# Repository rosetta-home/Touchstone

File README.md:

# Open Source Indoor Air Quality Sensor
An open hardware and software indoor air quality sensor provided by the [National Association of REALTORS](http://realtor.org) and [CRT Labs](https://crtlabs.org) in collaboration with the [Built Environment Research Group](http://built-envi.com/) at Illinois Institute of Technology.

**Features**:
* Can measure upto 8 indoor environmental quality parameters (listed below)
* Atmel ATmega328P 16MHz 8-bit processor (based on Arduino platform)
* Genuine FTDI chip for serial communication with host computer
* Mini RGB LED for status and notification
* Programmable button for custom actions such as reset, configuration, etc.
* Long range wireless data transfer using FSK radio (no dependence on WiFi, cellular, etc.)
* Small footprint PCB board (less than 2x2 inches or 50x50mm)
* Low power requirements (35mA idle with all sensors running, 190mA peak during wireless data transfer)

**Measurement Points**:
* Temperature (Si7021)
* Relative Humidity (Si7021)
* VOC (Volatile Organic Compounds) (CCS811/IAQ-Core)
* CO2 (MH-z19)
* Particulate Matter, PM2.5 (PMS7003)
* Barometric Pressure (BMP280)
* Light Intensity (TSL2591)
* Sound Intensity (Electret Microphone)

**Connectivity**:
* FSK radio (RFM69HW 915MHz)
* MicroUSB (FTDI FX231XQ)

License:
Apache License Version 2.0

For the Raspberry Pi HAT, please visit the [PiAQ Website](http://piaq.io) and [repository](https://github.com/NationalAssociationOfRealtors/PiAQ)

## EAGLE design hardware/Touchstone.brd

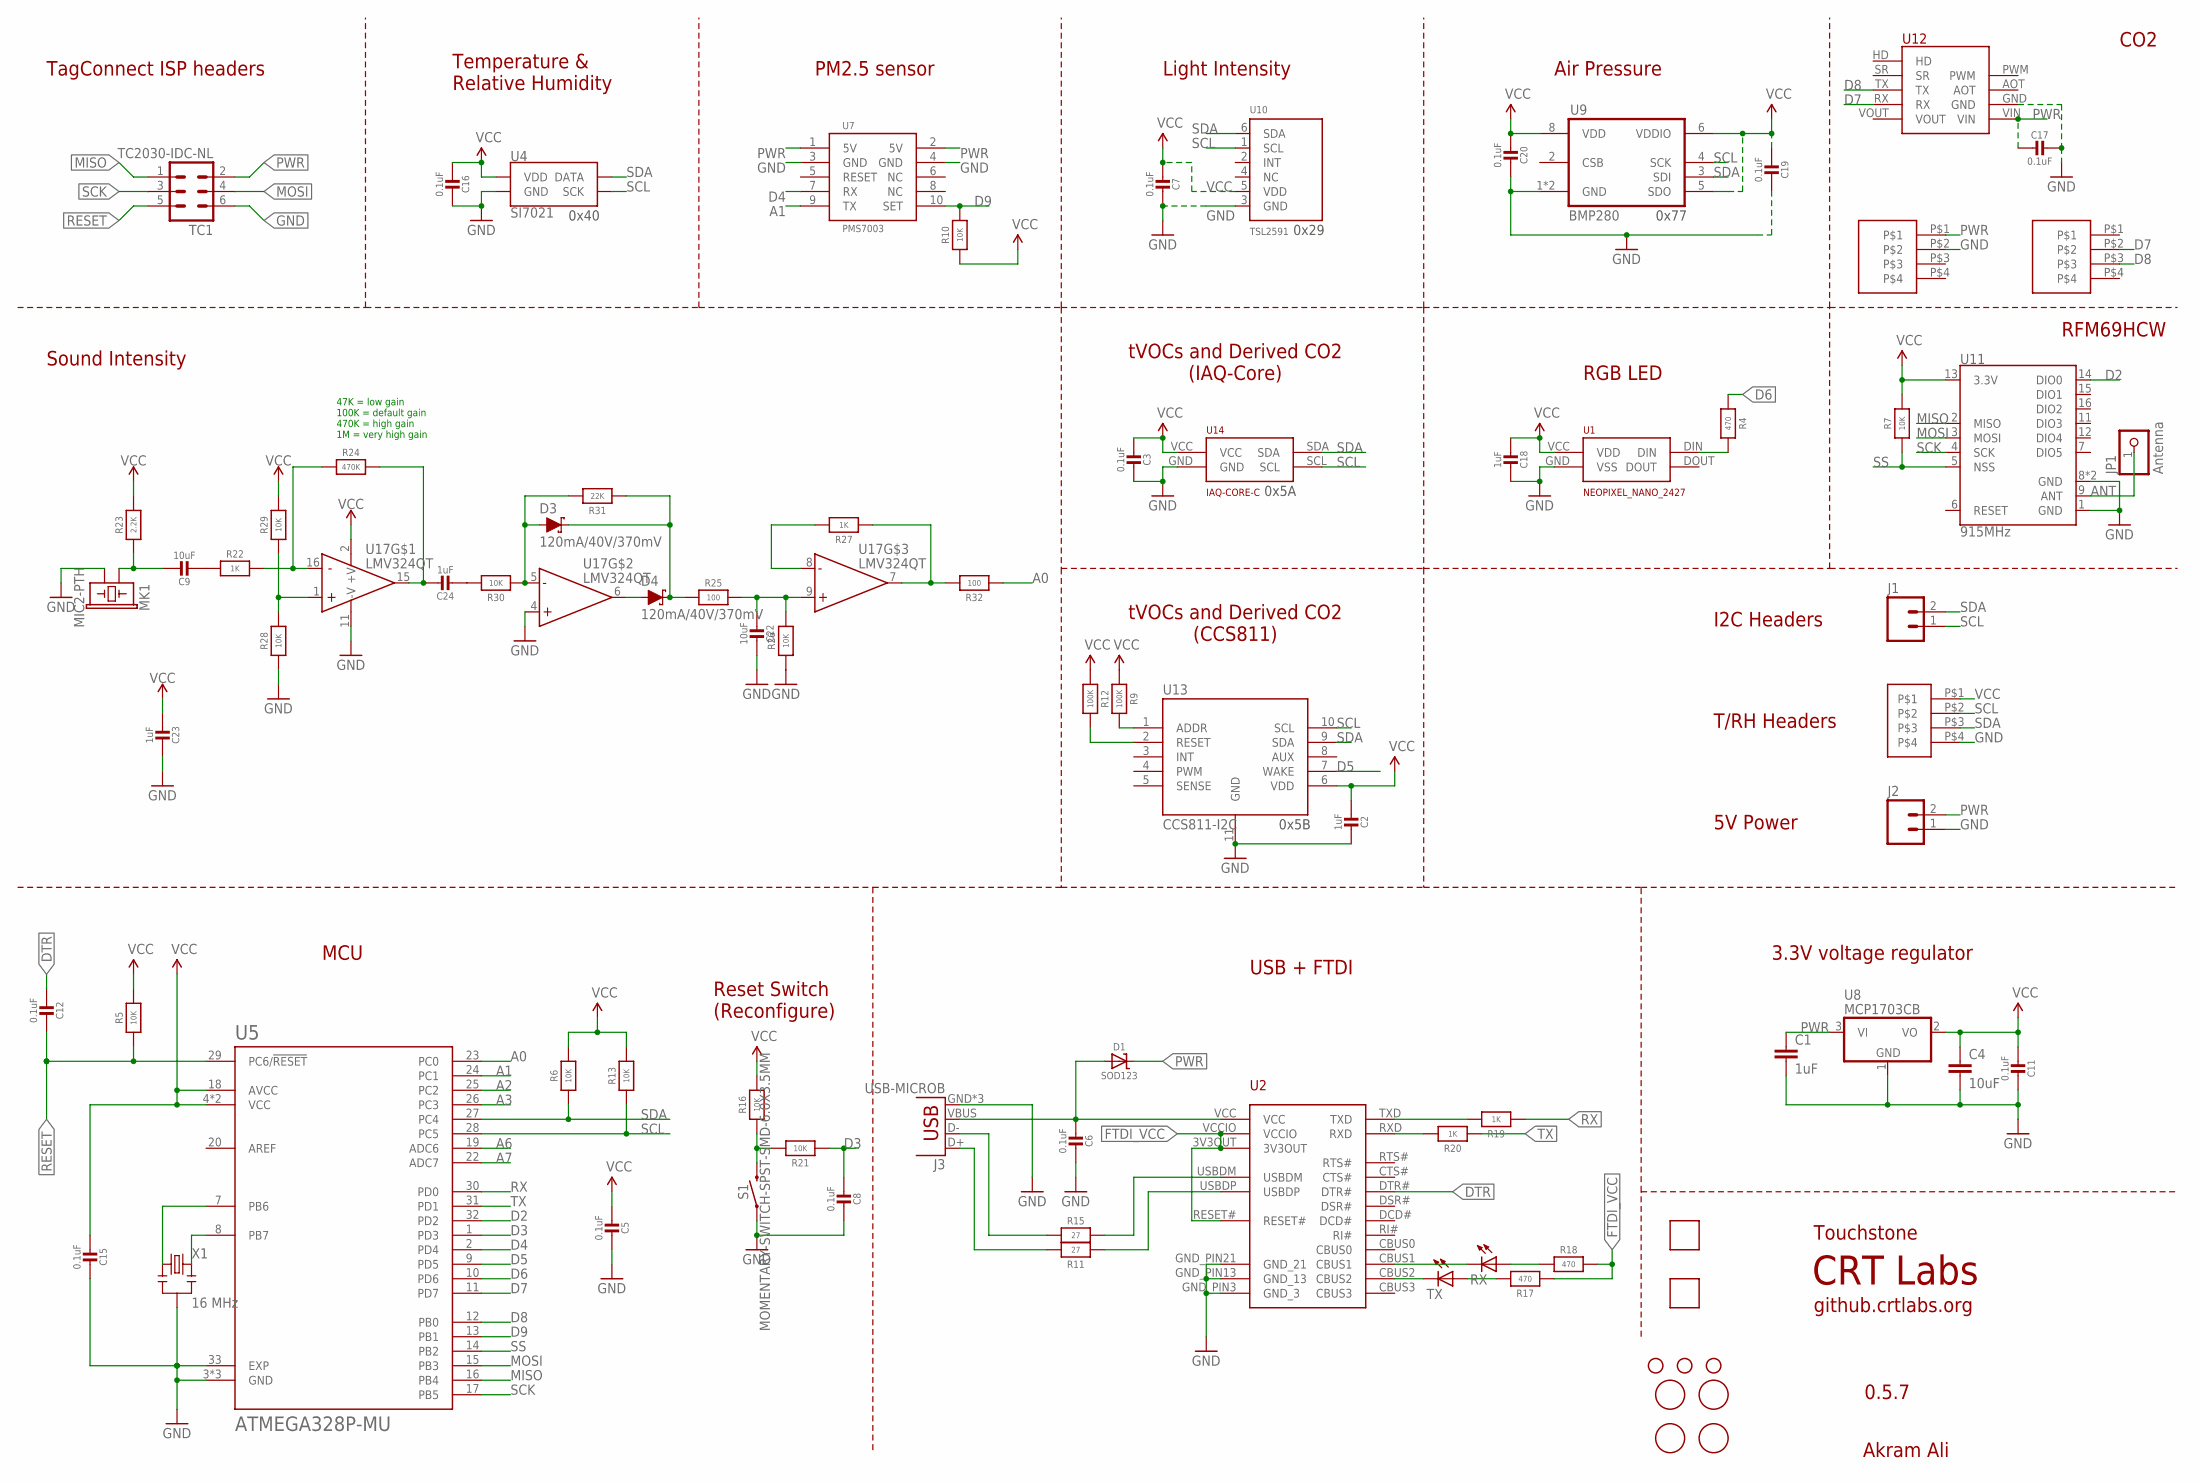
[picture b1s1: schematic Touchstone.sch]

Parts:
C1: 1uF; 0805; MPN CC0805ZRY5V8BB105
C2, C18, C23, C24: 1uF; MICROBUILDER__0402MP; MPN CC0402KRX5R6BB105
C3, C5, C6, C7, C8, C11, C12, C15, C16, C17, C19, C20: 0.1uF; MICROBUILDER__0402MP; MPN GRM155R71C104KA88J
C4: 10uF; 0805; MPN CC0805KKX5R6BB106
C9, C22: 10uF; MICROBUILDER__0402MP; MPN GRJ155R60J106ME11D
D1: SOD123; MICROBUILDER_SOD-123; MPN SD103AW-13-F
D3, D4: 120mA/40V/370mV; SOD-523; MPN RB751S40T1G
H1, H2, H3: STAND-OFF
J1, J2: M02PTH; 1X02
J3: USB-MICROB; MPN ZX62-B-5PA(33)
JP1: Antenna; 1X01-CLEANBIG; MPN Helical antenna
MK1: MIC2-PTH; MICROPHONE-PTH-4.0MM; MPN TOM-1545P-R
R4, R17, R18: 470; MICROBUILDER__0402MP; MPN RC0402JR-07470RL
R5, R6, R7, R10, R13, R16, R21, R26, R28, R29, R30: 10K; MICROBUILDER__0402MP; MPN RC0402JR-0710KL
R9, R12: 100K; MICROBUILDER__0402MP; MPN RC0402FR-07100KL
R11, R15: 27; MICROBUILDER__0402MP; MPN RC0402JR-0727RL
R19, R20, R22, R27: 1K; MICROBUILDER__0402MP; MPN RC0402JR-071KL
R23: 2.2K; MICROBUILDER__0402MP; MPN RC0402FR-072K2L
R24: 470K; MICROBUILDER__0402MP; MPN RC0402FR-071ML
R25, R32: 100; MICROBUILDER__0402MP; MPN RC0402FR-07100RL
R31: 22K; MICROBUILDER__0402MP; MPN RC0402JR-0722KL
RX: LEDCHIPLED_0805; CHIPLED_0805; MPN LG R971-KN-1
S1: MOMENTARY-SWITCH-SPST-SMD-6.0X3.5MM; TACTILE_SWITCH_SMD_6.0X3.5MM; MPN RS-032G05A3-SM RT
TC1: TC2030-IDC-NL
TX: LEDCHIPLED_0805; CHIPLED_0805; MPN LG R971-KN-1
U1: NEOPIXEL_NANO_2427; SK6805-2427; MPN 3484
U2: FT231XQ-R; FTDI_FT231XQ-R_PACKAGE; MPN FT231XQ-R
U4: SI7021; DFN-6-3X3-SI7021; MPN SI7021-A20-GM1
U5: ATMEGA328P-MU; QFN50P500X500X100-33N; MPN ATMEGA328P-MU
U7: PMS7003; PMS7003_RECEPTACLE_1.27MM_2X5; MPN 20021311-00012T4LF
U8: MCP1703CB; SOT23; MPN MCP1703T-3302E/CB
U9: BMP280; MPN BMP280
U10: TSL2591; DFN6_TAOS; MPN TSL25911FN
U11: 915MHz; RFM69HCW-XXXS2; MPN RFM69HCW
U12: MH-Z19; MPN MH-z19
U13: CCS811-I2C; LGA; MPN CCS811
U14: IAQ-CORE-C; MPN IAQ-CORE-C
U15: VLP-450-F; MPN VLP-650-F
U16: VLP-450-F; MPN VLP-550-F
U17: LMV324QT; QFN-16_3X3; MPN LM324QT
U$1, U$2, U$3, U$7: FIDUCIAL; FIDUCIAL_1MM
U$4, U$5: 0878980426; CONN_4POS_VERT_2.54_SMD; MPN 0878980426
U$6: CONN_HDR_1.27MM_SMD_4POS; MPN M50-3630442
X1: 16 MHz; RESONATOR-SMD; MPN CSTCE16M0V53-R0

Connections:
A0: R32.1, U5.23 (PC0)
A1: U5.24 (PC1), U7.9 (TX)
A2: U5.25 (PC2)
A3: U5.26 (PC3)
A6: U5.19 (ADC6)
A7: U5.22 (ADC7)
AMP: C24.1, R24.2, U17.15 (OUT)
ANT: JP1.1, U11.9 (ANT)
D2: U5.32 (PD2), U11.14 (DIO0)
D3: C8.2, R21.1, U5.1 (PD3)
D4: U5.2 (PD4), U7.7 (RX)
D5: U5.9 (PD5), U13.7 (WAKE)
D6: R4.1, U5.10 (PD6)
D7: U5.11 (PD7), U12.RX, U$5.P$2
D8: U5.12 (PB0), U12.TX, U$5.P$3
D9: R10.2, U5.13 (PB1), U7.10 (SET)
DTR: C12.2, U2.DTR#
FTDI_VCC: R17.1, R18.2, U2.3V3OUT, U2.RESET#, U2.VCCIO
GND: C1.2, C2.1, C3.1, C4.2, C5.1, C6.1, C7.1, C8.1, C11.1, C15.1, C16.1, C17.1, C18.1, C19.1, C20.1, C22.1, C23.1, J2.1, J3.GND, J3.MT1 (GND), J3.MT2 (GND), MK1.GND (2), R26.1, R28.1, S1.1, TC1.6, U1.GND (VSS), U2.GND_PIN3 (GND_3), U2.GND_PIN13 (GND_13), U2.GND_PIN21 (GND_21), U4.GND, U5.3 (GND), U5.5 (GND), U5.21 (GND), U5.33 (EXP), U7.3 (GND), U7.4 (GND), U8.1 (GND), U9.1 (GND), U9.7 (GND), U10.3 (GND), U11.1 (GND), U11.8 (GND), U11.10 (GND), U12.GND, U13.11 (GND), U14.GND, U17.4 (+IN), U17.11 (-V), U$4.P$2, U$6.P$4, X1.2
MISO: TC1.1, U5.16 (PB4), U11.2 (MISO)
MOSI: TC1.4, U5.15 (PB3), U11.3 (MOSI)
unnamed: R4.2, U1.DIN
unnamed: R20.2, U2.RXD
unnamed: R19.2, U2.TXD
unnamed: U5.8 (PB7), X1.3
unnamed: U5.7 (PB6), X1.1
unnamed: R12.2, U13.2 (RESET)
unnamed: R16.1, R21.2, S1.2
unnamed: C9.2, R22.1
unnamed: C9.1, MK1.OUT (1), R23.1
unnamed: R22.2, R24.1, U17.16 (-IN)
unnamed: R9.2, U13.1 (ADDR)
unnamed: D3.C, D4.C, R25.1, R31.1
unnamed: R27.2, U17.8 (-IN)
unnamed: RX.C, U2.CBUS1
unnamed: TX.C, U2.CBUS2
unnamed: C24.2, R30.2
unnamed: C22.2, R25.2, R26.2, U17.9 (+IN)
unnamed: D4.A, U17.6 (OUT)
unnamed: D3.A, R30.1, R31.2, U17.5 (-IN)
unnamed: R15.2, U2.USBDM
unnamed: R11.1, U2.USBDP
unnamed: R18.1, RX.A
unnamed: R17.2, TX.A
unnamed: J3.D-, R15.1
unnamed: J3.D+, R11.2
PWR: C1.1, C17.2, D1.C, J2.2, TC1.2, U7.1 (5V), U7.2 (5V), U8.3 (VI), U12.VIN, U$4.P$1
RESET: C12.1, R5.1, TC1.5, U5.29 (PC6/!RESET)
RX: R19.1, U5.30 (PD0)
SCK: TC1.3, U5.17 (PB5), U11.4 (SCK)
SCL: J1.1, R13.1, U4.SCK, U5.28 (PC5), U9.4 (SCK), U10.1 (SCL), U13.10 (SCL), U14.SCL, U$6.P$2
SDA: J1.2, R6.1, U4.DATA, U5.27 (PC4), U9.3 (SDI), U10.6 (SDA), U13.9 (SDA), U14.SDA, U$6.P$3
SS: R7.1, U5.14 (PB2), U11.5 (NSS)
TX: R20.1, U5.31 (PD1)
VBUS: C6.2, D1.A, J3.VBUS, U2.VCC
VCC: C2.2, C3.2, C4.1, C5.2, C7.2, C11.2, C15.2, C16.2, C18.2, C19.2, C20.2, C23.2, R5.2, R6.2, R7.2, R9.1, R10.1, R12.1, R13.2, R16.2, R23.2, R29.2, U1.VCC (VDD), U4.VDD, U5.4 (VCC), U5.6 (VCC), U5.18 (AVCC), U8.2 (VO), U9.5 (SDO), U9.6 (VDDIO), U9.8 (VDD), U10.5 (VDD), U11.13 (3.3V), U13.6 (VDD), U14.VCC, U17.2 (+V), U$6.P$1
VCC/2: R28.2, R29.1, U17.1 (+IN)
_OUT: R27.1, R32.2, U17.7 (OUT)

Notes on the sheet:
Light Intensity
tVOCs and Derived CO2 (IAQ-Core)
Air Pressure
Sound Intensity
Temperature & Relative Humidity
TagConnect ISP headers
3.3V voltage regulator
CRT Labs
Touchstone
Akram Ali
USB + FTDI
0x5A
0x77
0.5.7
github.crtlabs.org
0x29
RGB LED
I2C Headers
PM2.5 sensor
RFM69HCW
MCU
CO2
tVOCs and Derived CO2 (CCS811)
5V Power
0x5B
0x40
T/RH Headers
Reset Switch (Reconfigure)
47K = low gain 100K = default gain 470K = high gain 1M = very high gain

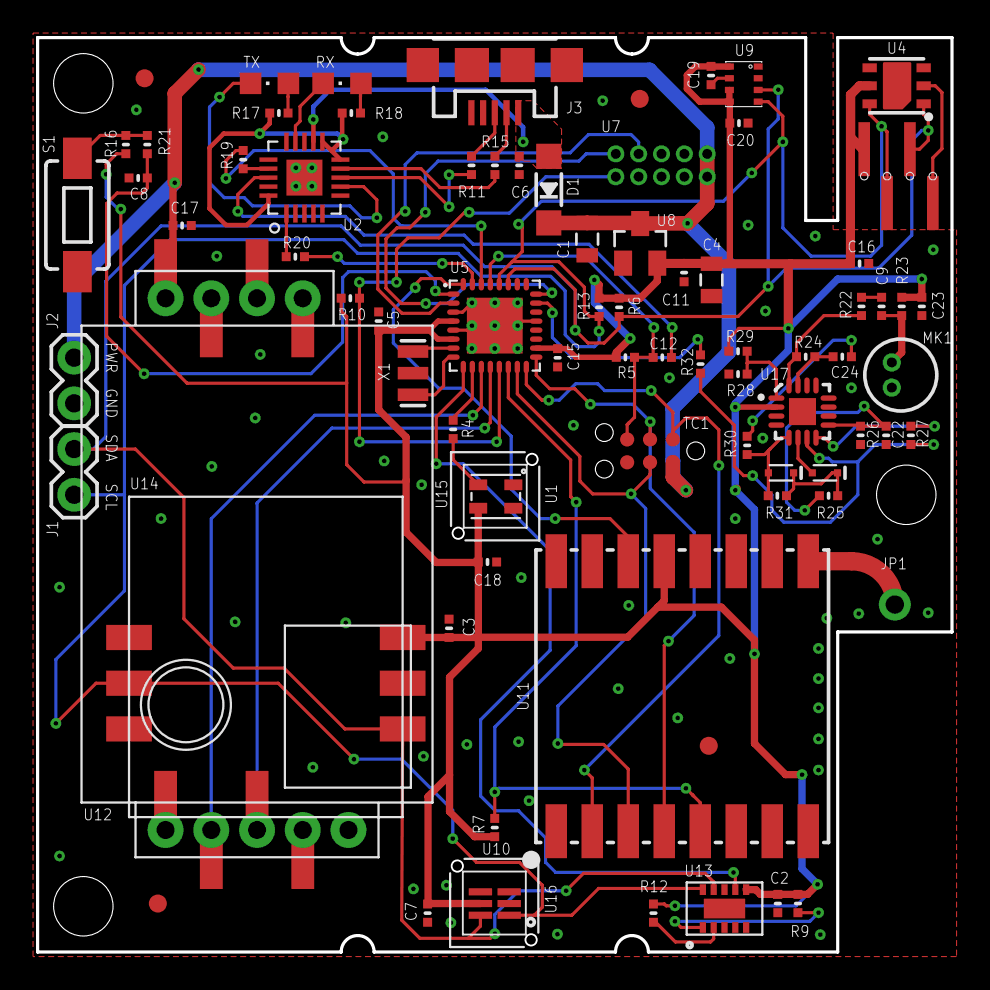
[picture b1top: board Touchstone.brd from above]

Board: 2 copper layers, 50.8 x 50.8 mm, 85 parts (1 on the bottom side), 54 nets.

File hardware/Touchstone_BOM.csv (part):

"Part";"Value";"Device";"Package";"Description";"AVAILABILITY";"DESCRIPTION";"MF";"MP";"MPN";"OC_NEWARK";"PACKAGE";"PRICE";"PROD_ID";"SF_ID";"SF_SKU";"VALUE";
"C1";"1uF";"CAP0805";"0805";"Capacitor";"";"";"";"";"CC0805ZRY5V8BB105";"";"";"";"";"";"";"";
"C2";"1uF";"MICROBUILDER_CAP_CERAMIC_0402MP";"MICROBUILDER__0402MP";"Ceramic Capacitors";"";"";"";"";"CC0402KRX5R6BB105";"";"";"";"";"";"";"";
"C3";"0.1uF";"MICROBUILDER_CAP_CERAMIC_0402MP";"MICROBUILDER__0402MP";"Ceramic Capacitors";"";"";"";"";"GRM155R71C104KA88J";"";"";"";"";"";"";"";
"C4";"10uF";"CAP0805";"0805";"Capacitor";"";"";"";"";"CC0805KKX5R6BB106";"";"";"";"";"";"";"";
"C5";"0.1uF";"MICROBUILDER_CAP_CERAMIC_0402MP";"MICROBUILDER__0402MP";"Ceramic Capacitors";"";"";"";"";"GRM155R71C104KA88J";"";"";"";"";"";"";"";
"C6";"0.1uF";"MICROBUILDER_CAP_CERAMIC_0402MP";"MICROBUILDER__0402MP";"Ceramic Capacitors";"";"";"";"";"GRM155R71C104KA88J";"";"";"";"";"";"";"";
"C7";"0.1uF";"MICROBUILDER_CAP_CERAMIC_0402MP";"MICROBUILDER__0402MP";"Ceramic Capacitors";"";"";"";"";"GRM155R71C104KA88J";"";"";"";"";"";"";"";
"C8";"0.1uF";"MICROBUILDER_CAP_CERAMIC_0402MP";"MICROBUILDER__0402MP";"Ceramic Capacitors";"";"";"";"";"GRM155R71C104KA88J";"";"";"";"";"";"";"";
"C9";"10uF";"MICROBUILDER_CAP_CERAMIC_0402MP";"MICROBUILDER__0402MP";"Ceramic Capacitors";"";"";"";"";"GRJ155R60J106ME11D";"";"";"";"";"";"";"";
"C11";"0.1uF";"MICROBUILDER_CAP_CERAMIC_0402MP";"MICROBUILDER__0402MP";"Ceramic Capacitors";"";"";"";"";"GRM155R71C104KA88J";"";"";"";"";"";"";"";
"C12";"0.1uF";"MICROBUILDER_CAP_CERAMIC_0402MP";"MICROBUILDER__0402MP";"Ceramic Capacitors";"";"";"";"";"GRM155R71C104KA88J";"";"";"";"";"";"";"";
"C15";"0.1uF";"MICROBUILDER_CAP_CERAMIC_0402MP";"MICROBUILDER__0402MP";"Ceramic Capacitors";"";"";"";"";"GRM155R71C104KA88J";"";"";"";"";"";"";"";
"C16";"0.1uF";"MICROBUILDER_CAP_CERAMIC_0402MP";"MICROBUILDER__0402MP";"Ceramic Capacitors";"";"";"";"";"GRM155R71C104KA88J";"";"";"";"";"";"";"";
"C17";"0.1uF";"MICROBUILDER_CAP_CERAMIC_0402MP";"MICROBUILDER__0402MP";"Ceramic Capacitors";"";"";"";"";"GRM155R71C104KA88J";"";"";"";"";"";"";"";
"C18";"1uF";"MICROBUILDER_CAP_CERAMIC_0402MP";"MICROBUILDER__0402MP";"Ceramic Capacitors";"";"";"";"";"CC0402KRX5R6BB105";"";"";"";"";"";"";"";
"C19";"0.1uF";"MICROBUILDER_CAP_CERAMIC_0402MP";"MICROBUILDER__0402MP";"Ceramic Capacitors";"";"";"";"";"GRM155R71C104KA88J";"";"";"";"";"";"";"";
"C20";"0.1uF";"MICROBUILDER_CAP_CERAMIC_0402MP";"MICROBUILDER__0402MP";"Ceramic Capacitors";"";"";"";"";"GRM155R71C104KA88J";"";"";"";"";"";"";"";
"C22";"10uF";"MICROBUILDER_CAP_CERAMIC_0402MP";"MICROBUILDER__0402MP";"Ceramic Capacitors";"";"";"";"";"GRJ155R60J106ME11D";"";"";"";"";"";"";"";
"C23";"1uF";"MICROBUILDER_CAP_CERAMIC_0402MP";"MICROBUILDER__0402MP";"Ceramic Capacitors";"";"";"";"";"CC0402KRX5R6BB105";"";"";"";"";"";"";"";
"C24";"1uF";"MICROBUILDER_CAP_CERAMIC_0402MP";"MICROBUILDER__0402MP";"Ceramic Capacitors";"";"";"";"";"CC0402KRX5R6BB105";"";"";"";"";"";"";"";
"D1";"SOD123";"MICROBUILDER_DIODE-SCHOTTKYSOD-123";"MICROBUILDER_SOD-123";"";"";"";"";"";"SD103AW-13-F";"";"";"";"";"";"";"";
"D3";"120mA/40V/370mV";"DIODE-SCHOTTKY-RB751S40";"SOD-523";"Schottky diode";"";"";"";"";"RB751S40T1G";"";"";"";"DIO-11018";"";"";"120mA/40V/370mV";
"D4";"120mA/40V/370mV";"DIODE-SCHOTTKY-RB751S40";"SOD-523";"Schottky diode";"";"";"";"";"RB751S40T1G";"";"";"";"DIO-11018";"";"";"120mA/40V/370mV";
"H1";"STAND-OFF";"STAND-OFF";"STAND-OFF";"#4 Stand Off";"";"";"";"";"";"";"";"";"";"";"";"";
"H2";"STAND-OFF";"STAND-OFF";"STAND-OFF";"#4 Stand Off";"";"";"";"";"";"";"";"";"";"";"";"";
"H3";"STAND-OFF";"STAND-OFF";"STAND-OFF";"#4 Stand Off";"";"";"";"";"";"";"";"";"";"";"";"";
"J1";"";"M02PTH";"1X02";"Standard 2-pin 0.1" header. Use with";"";"";"";"";"";"";"";"";"";"";"";"";
"J2";"";"M02PTH";"1X02";"Standard 2-pin 0.1" header. Use with";"";"";"";"";"";"";"";"";"";"";"";"";
"J3";"USB-MICROB";"USB-MICROB";"USB-MICROB";"USB Connectors";"";"";"";"";"ZX62-B-5PA(33)";"";"";"";"CONN-09505";"";"";"";
"JP1";"Antenna";"PINHD-1X1CB";"1X01-CLEANBIG";"Pin header 1x1 for 0.1" spacing";"";"";"";"";"Helical antenna";"";"";"";"";"";"";"";
"MK1";"MIC2-PTH";"MIC2-PTH";"MICROPHONE-PTH-4.0MM";"Mini Electret Microphone";"";"";"";"";"TOM-1545P-R";"";"";"";"COMP-08856";"COM-08635";"";"";
"R4";"470";"MICROBUILDER_RESISTOR_0402MP";"MICROBUILDER__0402MP";"Resistors";"";"";"";"";"RC0402JR-07470RL";"";"";"";"";"";"";"";
"R5";"10K";"MICROBUILDER_RESISTOR_0402MP";"MICROBUILDER__0402MP";"Resistors";"";"";"";"";"RC0402JR-0710KL";"";"";"";"";"";"";"";
"R6";"10K";"MICROBUILDER_RESISTOR_0402MP";"MICROBUILDER__0402MP";"Resistors";"";"";"";"";"RC0402JR-0710KL";"";"";"";"";"";"";"";
"R7";"10K";"MICROBUILDER_RESISTOR_0402MP";"MICROBUILDER__0402MP";"Resistors";"";"";"";"";"RC0402JR-0710KL";"";"";"";"";"";"";"";
"R9";"100K";"MICROBUILDER_RESISTOR_0402MP";"MICROBUILDER__0402MP";"Resistors";"";"";"";"";"RC0402FR-07100KL";"";"";"";"";"";"";"";
"R10";"10K";"MICROBUILDER_RESISTOR_0402MP";"MICROBUILDER__0402MP";"Resistors";"";"";"";"";"RC0402JR-0710KL";"";"";"";"";"";"";"";
"R11";"27";"MICROBUILDER_RESISTOR_0402MP";"MICROBUILDER__0402MP";"Resistors";"";"";"";"";"RC0402JR-0727RL";"";"";"";"";"";"";"";
"R12";"100K";"MICROBUILDER_RESISTOR_0402MP";"MICROBUILDER__0402MP";"Resistors";"";"";"";"";"RC0402FR-07100KL";"";"";"";"";"";"";"";
"R13";"10K";"MICROBUILDER_RESISTOR_0402MP";"MICROBUILDER__0402MP";"Resistors";"";"";"";"";"RC0402JR-0710KL";"";"";"";"";"";"";"";
"R14";"100K";"MICROBUILDER_RESISTOR_0402MP";"MICROBUILDER__0402MP";"Resistors";"";"";"";"";"RC0402FR-07100KL";"";"";"";"";"";"";"";
"R15";"27";"MICROBUILDER_RESISTOR_0402MP";"MICROBUILDER__0402MP";"Resistors";"";"";"";"";"RC0402JR-0727RL";"";"";"";"";"";"";"";
"R16";"10K";"MICROBUILDER_RESISTOR_0402MP";"MICROBUILDER__0402MP";"Resistors";"";"";"";"";"RC0402JR-0710KL";"";"";"";"";"";"";"";
"R17";"470";"MICROBUILDER_RESISTOR_0402MP";"MICROBUILDER__0402MP";"Resistors";"";"";"";"";"RC0402JR-07470RL";"";"";"";"";"";"";"";
"R18";"470";"MICROBUILDER_RESISTOR_0402MP";"MICROBUILDER__0402MP";"Resistors";"";"";"";"";"RC0402JR-07470RL";"";"";"";"";"";"";"";
"R19";"1K";"MICROBUILDER_RESISTOR_0402MP";"MICROBUILDER__0402MP";"Resistors";"";"";"";"";"RC0402JR-071KL";"";"";"";"";"";"";"";
"R20";"1K";"MICROBUILDER_RESISTOR_0402MP";"MICROBUILDER__0402MP";"Resistors";"";"";"";"";"RC0402JR-071KL";"";"";"";"";"";"";"";
"R21";"10K";"MICROBUILDER_RESISTOR_0402MP";"MICROBUILDER__0402MP";"Resistors";"";"";"";"";"RC0402JR-0710KL";"";"";"";"";"";"";"";
"R22";"1K";"MICROBUILDER_RESISTOR_0402MP";"MICROBUILDER__0402MP";"Resistors";"";"";"";"";"RC0402JR-071KL";"";"";"";"";"";"";"";
"R23";"2.2K";"MICROBUILDER_RESISTOR_0402MP";"MICROBUILDER__0402MP";"Resistors";"";"";"";"";"RC0402FR-072K2L";"";"";"";"";"";"";"";
"R24";"470K";"MICROBUILDER_RESISTOR_0402MP";"MICROBUILDER__0402MP";"Resistors";"";"";"";"";"RC0402JR-07470KL";"";"";"";"";"";"";"";
"R25";"100";"MICROBUILDER_RESISTOR_0402MP";"MICROBUILDER__0402MP";"Resistors";"";"";"";"";"RC0402FR-07100RL";"";"";"";"";"";"";"";
"R26";"10K";"MICROBUILDER_RESISTOR_0402MP";"MICROBUILDER__0402MP";"Resistors";"";"";"";"";"RC0402JR-0710KL";"";"";"";"";"";"";"";
"R27";"1K";"MICROBUILDER_RESISTOR_0402MP";"MICROBUILDER__0402MP";"Resistors";"";"";"";"";"RC0402JR-071KL";"";"";"";"";"";"";"";
"R28";"10K";"MICROBUILDER_RESISTOR_0402MP";"MICROBUILDER__0402MP";"Resistors";"";"";"";"";"RC0402JR-0710KL";"";"";"";"";"";"";"";
"R29";"10K";"MICROBUILDER_RESISTOR_0402MP";"MICROBUILDER__0402MP";"Resistors";"";"";"";"";"RC0402JR-0710KL";"";"";"";"";"";"";"";
"R30";"10K";"MICROBUILDER_RESISTOR_0402MP";"MICROBUILDER__0402MP";"Resistors";"";"";"";"";"RC0402JR-0710KL";"";"";"";"";"";"";"";
"R31";"22K";"MICROBUILDER_RESISTOR_0402MP";"MICROBUILDER__0402MP";"Resistors";"";"";"";"";"RC0402JR-0722KL";"";"";"";"";"";"";"";
"R32";"100";"MICROBUILDER_RESISTOR_0402MP";"MICROBUILDER__0402MP";"Resistors";"";"";"";"";"RC0402FR-07100RL";"";"";"";"";"";"";"";
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
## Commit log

2017-08-07 :lollipop: Added .gitattributes & .gitignore files
2017-08-07 init
2017-08-07 Adds arduino libraries as submodules
2017-08-14 Added pullups on CCS811's signal lines
    RESET AND WAKE lines pulled up by default
2017-08-14 Added SMD pads for T/RH breakout
2017-08-14 Version number change; minor adjustments
    - Changed version number to 0.5.7 (new versioning format)
    - silkscreen adjustments
    - some schematic rearrangements
2017-08-15 Added reset button
    - added momentary tactile button for resetting device (reconfiguring,
    not power cycle)
    - added other circuitry for button
    - moved I2C headers to make space for reset button
    - several traces redone to accomodate button
    - minor silkscreen adjustment
2017-08-15 Several routing adjustments
    - PMS7003 TX rewired from D3 to A1 (D3 is INT pin)
    - Button reqired from A1 to D3 (same reason above)
    - adjusted several traces to account for the above rewiring
    - Added several GND vias under MCU and FTDI (heatsink - may help a tiny
    bit)
    - minor silkscreen adjustments to account for above
2017-08-15 Added another fiducial marker
    - rearranged fiducials a bit
    - minor schematic update
2017-08-15 CRT silkscreen minor update
2017-08-24 firmware update - v0.56c
    Changed PMS7003 software serial to (A1, 4)
2017-08-28 Updated BOM
    MPN added for all parts
2017-08-28 Added BOM csv
2017-09-18 v0.5.7 - updated sound level circuit
    - Replaced MEMS mic with mini electret mic
    - Added analog circuitry for the mic
    - Some routing and silkscreen adjustments
2017-09-18 Fix conflicts
    - file got corrupted - fixed by restoring v7 file and saving as v8
2017-09-18 Updated BOM
    Added MPN for all components
2017-10-24 Firmware updated for v0.5.7
2017-10-30 Bug fixes
    - Removed pullup from WAKE pin of CSS811 (stopped chip from working)
    - Adjusted value of resistor on sound circuit to 1M (to increase gain to
    a LOT)
    - Minor trace and silkscreen adjustments
    - BOM update
2017-10-30 BOM update
    - 1M resistor added
    - 100K resistor removed
2017-10-30 PCB adjustments
    - Aligned a reistor properly
    - Removed some GND vias from underneath the MCU (paste was leaking
    through)
2017-12-05 Added gerbers and BOM
    - Also updated firmware for button interrupt, sound level stuff
2017-12-19 initial receiving of configuratoin commands
2017-12-20 handle commands and change LED color
2017-12-20 add LED Flash
2018-02-08 adds SPIFlash lib
2018-04-18 temp and humidity compensation
2019-03-01 sync
2019-03-03 pulled

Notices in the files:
parts and their libraries:
SparkFun-Connectors: Licensing: Creative Commons ShareAlike 4.0 International - https://creativecommons.org/licenses/by-sa/4.0
